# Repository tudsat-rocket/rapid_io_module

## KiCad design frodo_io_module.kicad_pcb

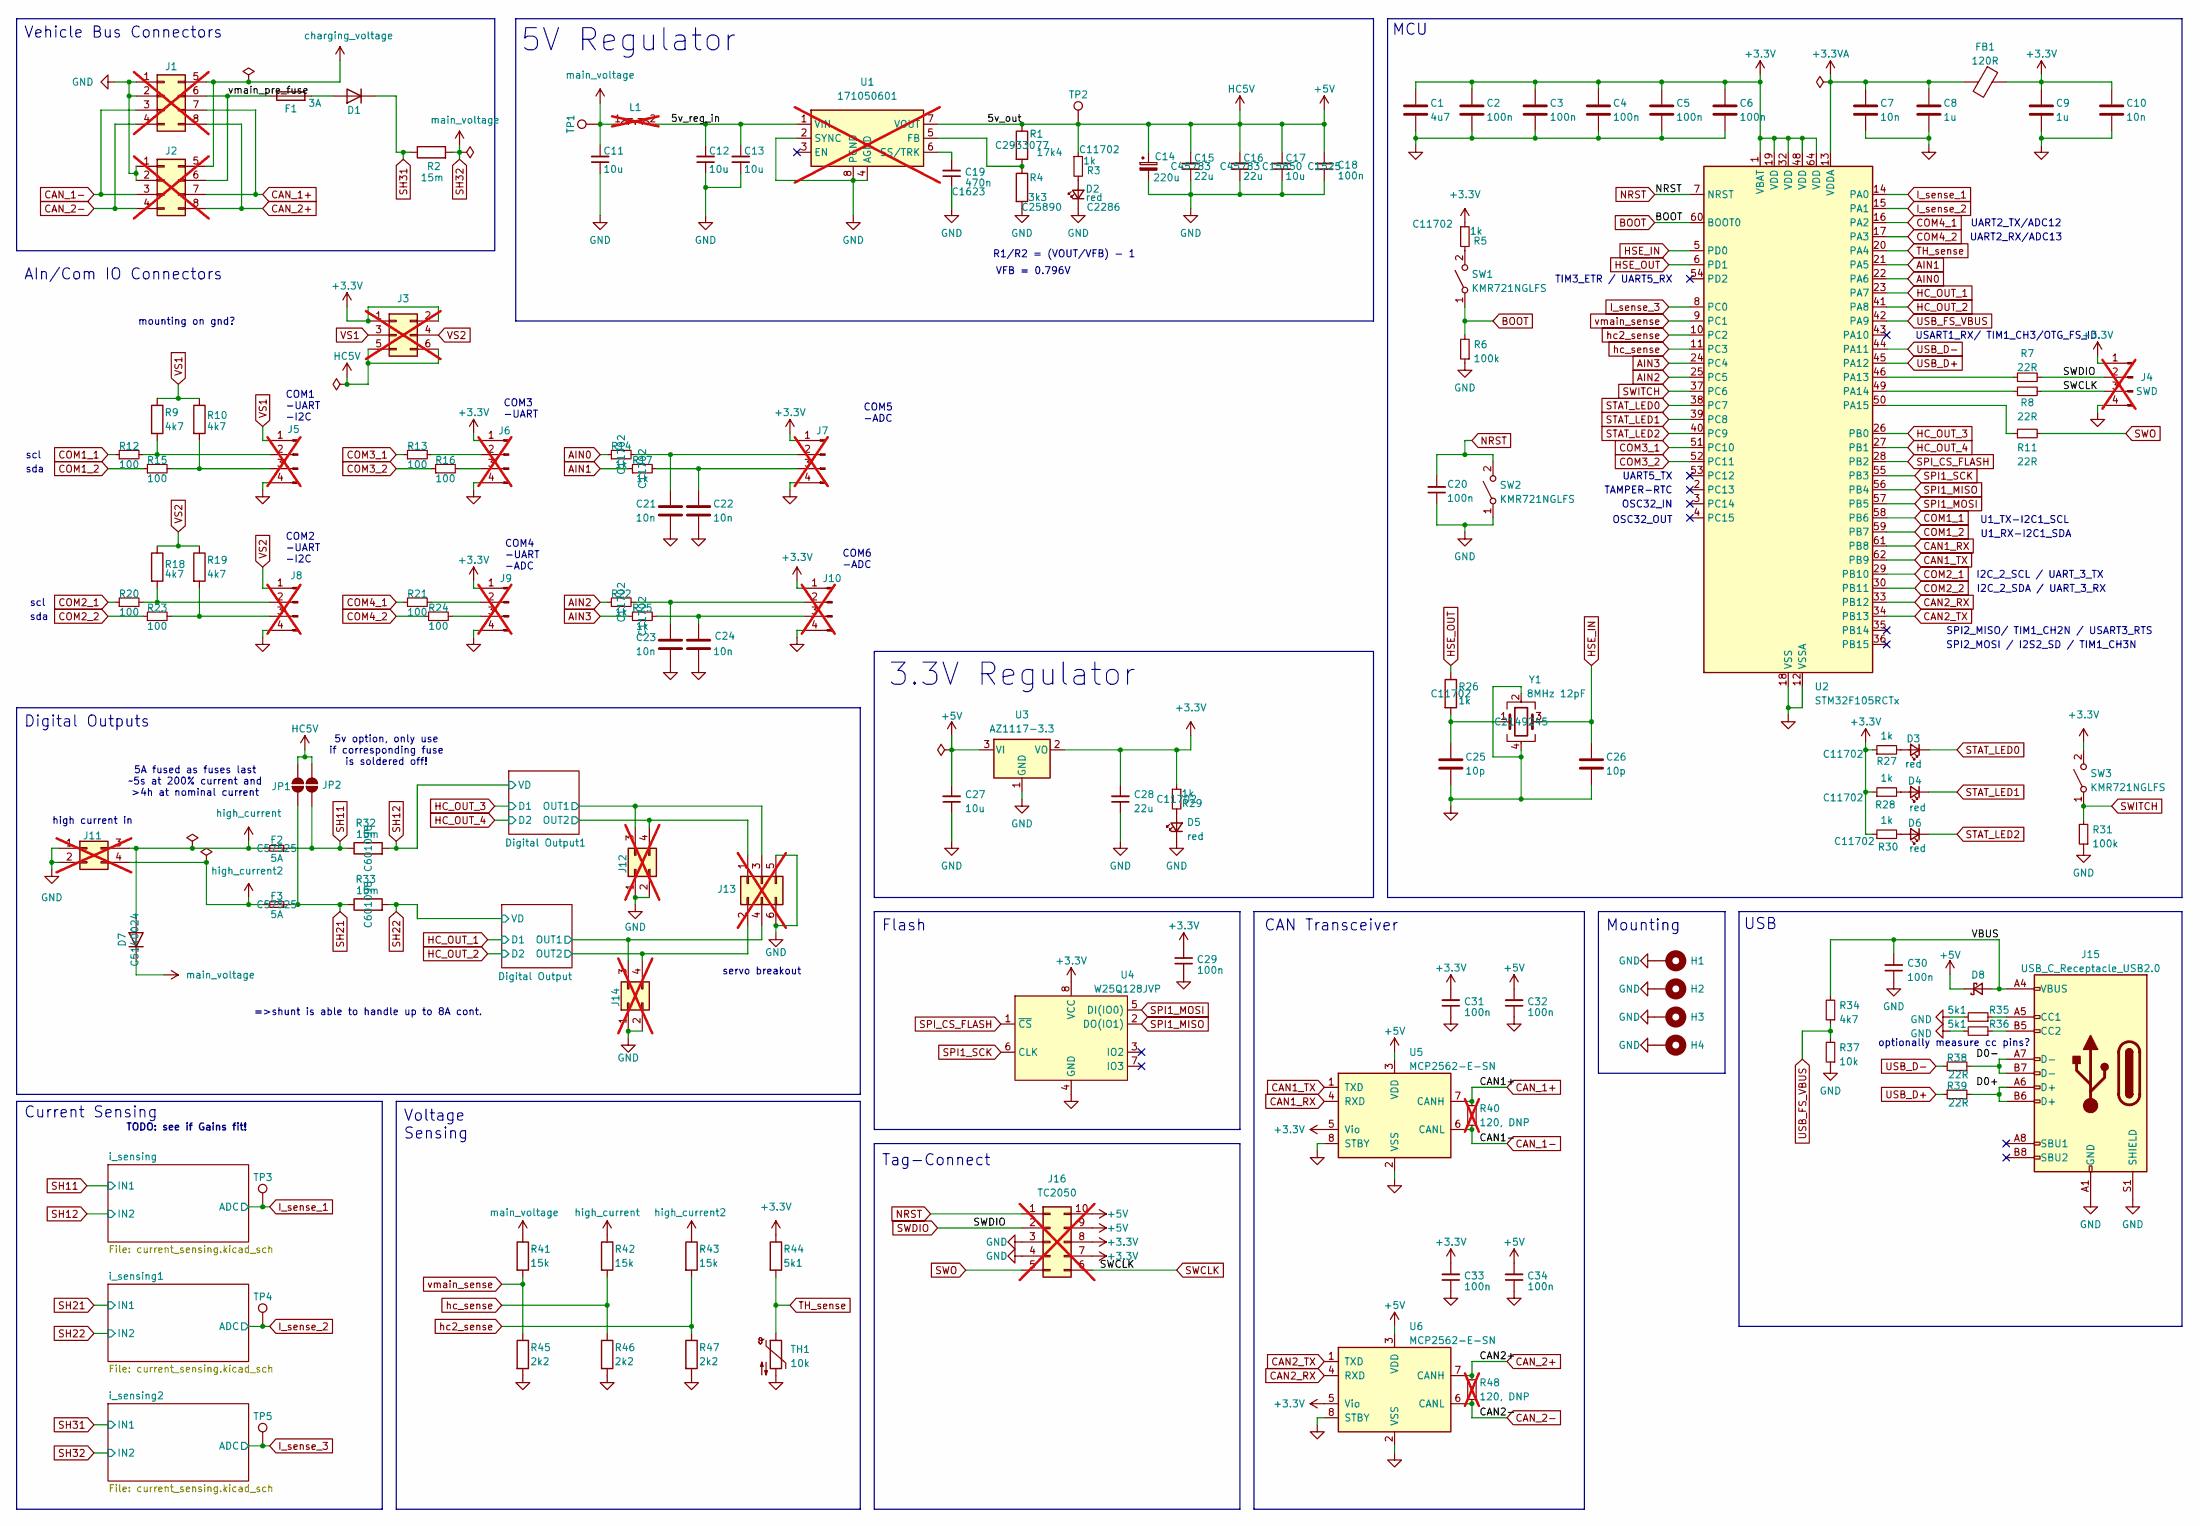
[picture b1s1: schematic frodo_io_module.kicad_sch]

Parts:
C1: 4u7; C_0402_1005Metric; LCSC# C23733
C2, C3, C4, C5, C6, C29, C31, C32, C33, C34: 100n; C_0402_1005Metric; LCSC# C1525
C7, C10: 10n; C_0402_1005Metric; LCSC# C15195
C8, C9: 1u; C_0402_1005Metric; LCSC# C52923
C11, C12, C13: 10u; C_0805_2012Metric; LCSC C440198
C14: 220u; CP_Elec_6.3x4.5; LCSC C5379968
C15, C16: 22u; C_0805_2012Metric; LCSC C45783
C17: 10u; C_0805_2012Metric; LCSC C15850
C18: 100n; C_0402_1005Metric; LCSC C1525
C19: 470n; C_0603_1608Metric; LCSC C1623
C20, C30: 100n; C_0402_1005Metric; Part# CL10B104KB8NNNC; LCSC C1525
C21, C22, C23, C24: 10n; C_0402_1005Metric; LCSC C15195
C25, C26: 10p; C_0402_1005Metric; LCSC# C32949
C27: 10u; C_0402_1005Metric; Part# CL31B106KAHNNNE; LCSC C15525
C28: 22u; C_0603_1608Metric; Part# GRM155R60J226ME11D; LCSC C59461
D1, D7: 700mV@5A; D_SMA; LCSC C5140024
D2: red; LED_0603_1608Metric; Part# XL-1608SURC-06; LCSC C2286
D3, D4, D5, D6: red; LED_0603_1608Metric; LCSC C2286
D8: D_SOD-123; Part# PMEG3020EH,115; LCSC C8598
F1: 3A; Fuse_1206_3216Metric_Pad1.42x1.75mm_HandSolder; LCSC C14165
F2, F3: 5A; Fuse_1206_3216Metric_Pad1.42x1.75mm_HandSolder; Part# 0466005.NRHF; LCSC C57525
FB1: 120R; L_0603_1608Metric; Part# BLM18PG121SN1D; LCSC# C14709
H1, H2, H3, H4: MountingHole_Pad; MountingHole_3.2mm_M3_Pad_Via; DigiKey# N/A
J1, J2: Conn_02x04_Top_Bottom; Molex_Micro-Fit_3.0_43045-0800_2x04_P3.00mm_Horizontal; LCSC x; not fitted
J3: Conn_02x03_Odd_Even; PinHeader_2x03_P1.27mm_Vertical_SMD; not fitted
J4: SWD; PinHeader_1x04_P2.54mm_Vertical; not fitted
J5, J6, J8, J9: JST-GH 4Pin; JST_GH_SM04B-GHS-TB_1x04-1MP_P1.25mm_Horizontal; not fitted
J7, J10: JST-GH 4Pin; JST_GH_BM04B-GHS-TBT_1x04-1MP_P1.25mm_Vertical; not fitted
J11: Molex_Micro-Fit_3.0_43045-0400_2x02_P3.00mm_Horizontal; LCSC# x; not fitted
J12, J14: Molex_Micro-Fit_3.0_43045-0400_2x02_P3.00mm_Horizontal; not fitted
J13: Conn_02x03_Odd_Even; PinHeader_2x03_P2.54mm_Vertical; not fitted
J15: USB_C_Receptacle_USB2.0; USB_C_Receptacle_Palconn_UTC16-G; Part# KH-TYPE-C-16P; LCSC C709357
J16: TC2050; Tag-Connect_TC2050-IDC-FP_2x05_P1.27mm_Vertical; not fitted
JP1, JP2: SolderJumper_2_Open; SolderJumper-2_P1.3mm_Open_RoundedPad1.0x1.5mm
L1: 2.2uH; L_Wurth_WE-PD2-5848; Part Number 744774022; not fitted
R1: 17k4; R_0402_1005Metric; LCSC C2933077
R2, R32, R33: 15m; R_1206_3216Metric_Pad1.30x1.75mm_HandSolder; Part# HoLR1206-1W-15mR-1%-75ppm; LCSC C601098
R3, R5, R14, R17, R22, R25, R26, R27, R28, R29, R30: 1k; R_0402_1005Metric; LCSC C11702
R4: 3k3; R_0402_1005Metric; LCSC C25890
R6, R31: 100k; R_0402_1005Metric; Part# RC0603FR-0710KL; LCSC C25741
R7, R8, R11: 22R; R_0402_1005Metric; Part# RC0603FR-0710KL; LCSC C25092
R9, R10, R18, R19: 4k7; R_0603_1608Metric_Pad0.98x0.95mm_HandSolder; LCSC C23162
R12, R13, R15, R16, R20, R21, R23, R24: 100; R_0402_1005Metric; Part# RC0402FR-07100RL; LCSC# C106232
R34: 4k7; R_0402_1005Metric; Part# RC0603FR-0710KL; LCSC C25900
R35, R36: 5k1; R_0402_1005Metric; Part# RC0603FR-075K1L; LCSC C25905
R37: 10k; R_0402_1005Metric; Part# RC0603FR-0710KL; LCSC C25744
R38, R39: 22R; R_0402_1005Metric; Part# RC0603FR-0722RL; LCSC C25092
R40, R48: 120, DNP; R_0603_1608Metric_Pad0.98x0.95mm_HandSolder; LCSC# x; not fitted
R41, R42, R43: 15k; R_0402_1005Metric; LCSC C25756
R44: 5k1; R_0402_1005Metric; LCSC C25905
R45, R46, R47: 2k2; R_0402_1005Metric; LCSC C25879
SW1, SW2, SW3: KMR721NGLFS; SW_SPST_TS-1088-xR020; Part# KMR721NGLFS; LCSC C720477
TH1: 10k; R_0603_1608Metric_Pad0.98x0.95mm_HandSolder; Part# NCP18XH103F03RB; LCSC# C13564
TP1, TP2, TP3, TP4, TP5: TestPoint; TestPoint_Pad_D1.0mm
U1: 171050601; TO-263-7_TabPin8; not fitted
U2: STM32F105RCTx; LQFP-64_10x10mm_P0.5mm; LCSC# C8345
U3: AZ1117-3.3; SOT-223-3_TabPin2; LCSC C92102
U4: W25Q128JVP; SOIC-8_5.3x5.3mm_P1.27mm; Part# W25Q128JVSIQ; LCSC# C97521
U5, U6: MCP2562-E-SN; SOIC-8_3.9x4.9mm_P1.27mm; Part# MCP2562T-E/SN; LCSC# C191417
Y1: 8MHz 12pF; Crystal_SMD_5032-4Pin_5.0x3.2mm; Part# 5TJ480000NYLBC; LCSC C2149245

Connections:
+3.3V: C1.1, C2.1, C3.1, C4.1, C5.1, C6.1, C9.1, C10.1, C28.2, C29.2, C31.2, C33.2, FB1.1, J3.1, J3.2, J4.1, J6.1, J7.1, J9.1, J10.1, J16.7, J16.8, R5.1, R27.1, R28.1, R29.1, R30.1, R44.1, SW3.2 (B), U2.1 (VBAT), U2.19 (VDD), U2.32 (VDD), U2.48 (VDD), U2.64 (VDD), U3.2 (VO), U4.8 (VCC), U5.5 (Vio), U6.5 (Vio); also elsewhere on the board
+3.3VA: C7.1, C8.1, FB1.2, U2.13 (VDDA)
+5V: C14.1, C15.2, C16.2, C17.2, C18.2, C27.2, C32.2, C34.2, D8.1 (K), J3.5, J3.6, J16.9, J16.10, JP1.2 (B), JP2.2 (B), R1.1, R3.1, TP2.1 (1_1), U1.7 (VOUT), U3.3 (VI), U5.3 (VDD), U6.3 (VDD)
/5v_reg_in: C12.2, C13.2, L1.2, U1.1 (VIN)
/D0+: J15.A6 (D+), J15.B6 (D+), R39.2
/D0-: J15.A7 (D-), J15.B7 (D-), R38.1
/Digital Output1/OUT1: J12.3, J13.3; also elsewhere on the board
/Digital Output1/OUT2: J12.4, J13.1; also elsewhere on the board
/Digital Output/OUT1: J13.4, J14.3; also elsewhere on the board
/Digital Output/OUT2: J13.2, J14.4; also elsewhere on the board
/VBUS: C30.2, D8.2 (A), J15.A4 (VBUS), J15.A9 (VBUS), J15.B4 (VBUS), J15.B9 (VBUS), R34.2
/vmain_pre_fuse: F1.1, J1.6, J2.6
AIN0: R14.1, U2.22 (PA6)
AIN1: R17.1, U2.21 (PA5)
AIN2: R22.1, U2.25 (PC5)
AIN3: R25.1, U2.24 (PC4)
BOOT: R6.2, SW1.1 (A), U2.60 (BOOT0)
CAN1_RX: U2.61 (PB8), U5.4 (RXD)
CAN1_TX: U2.62 (PB9), U5.1 (TXD)
CAN2_RX: U2.33 (PB12), U6.4 (RXD)
CAN2_TX: U2.34 (PB13), U6.1 (TXD)
CAN_1+: J1.7, J2.7, R40.1, U5.7 (CANH)
CAN_1-: J1.3, J2.3, R40.2, U5.6 (CANL)
CAN_2+: J1.8, J2.8, R48.1, U6.7 (CANH)
CAN_2-: J1.4, J2.4, R48.2, U6.6 (CANL)
COM1_1: R12.1, U2.58 (PB6)
COM1_2: R15.1, U2.59 (PB7)
COM2_1: R20.1, U2.29 (PB10)
COM2_2: R23.1, U2.30 (PB11)
COM3_1: R13.1, U2.51 (PC10)
COM3_2: R16.1, U2.52 (PC11)
COM4_1: R21.1, U2.16 (PA2)
COM4_2: R24.1, U2.17 (PA3)
GND: C1.2, C2.2, C3.2, C4.2, C5.2, C6.2, C7.2, C8.2, C9.2, C10.2, C11.1, C12.1, C13.1, C14.2, C15.1, C16.1, C17.1, C18.1, C19.1, C20.1, C21.2, C22.2, C23.2, C24.2, C25.2, C26.2, C27.1, C28.1, C29.1, C30.1, C31.1, C32.1, C33.1, C34.1, D2.1 (K), D5.1 (K), H1.1 (1_1), H2.1 (1_1), H3.1 (1_1), H4.1 (1_1), J1.1, J1.2, J2.1, J2.2, J4.4, J5.4, J6.4, J7.4, J8.4, J9.4, J10.4, J11.1, J11.2, J12.1, J12.2, J13.5, J13.6, J14.1, J14.2, J15.A1 (GND), J15.A12 (GND), J15.B1 (GND), J15.B12 (GND), J15.S1 (SHIELD), J16.3, J16.4, R4.2, R6.1, R31.1, R35.2, R36.2, R37.1, R45.2, R46.2, R47.2, SW2.1 (A), TH1.2, U1.2 (SYNC), U1.4 (AGND), U1.8 (PGND), U2.12 (VSSA), U2.18 (VSS), U2.31 (VSS), U2.47 (VSS), U2.63 (VSS), U3.1 (GND), U4.4 (GND), U5.2 (VSS), U5.8 (STBY), U6.2 (VSS), U6.8 (STBY), Y1.2, Y1.4; also elsewhere on the board
HC_OUT_1: U2.23 (PA7); also elsewhere on the board
HC_OUT_2: U2.41 (PA8); also elsewhere on the board
HC_OUT_3: U2.26 (PB0); also elsewhere on the board
HC_OUT_4: U2.27 (PB1); also elsewhere on the board
HSE_IN: C26.1, U2.5 (PD0), Y1.3
HSE_OUT: R26.1, U2.6 (PD1)
I_sense_1: TP3.1 (1_1), U2.14 (PA0); also elsewhere on the board
I_sense_2: TP4.1 (1_1), U2.15 (PA1); also elsewhere on the board
I_sense_3: TP5.1 (1_1), U2.8 (PC0); also elsewhere on the board
NRST: C20.2, J16.1, SW2.2 (B), U2.7 (NRST)
unnamed: C25.1, R26.2, Y1.1
unnamed: D1.2 (A), F1.2
unnamed: D2.2 (A), R3.2
unnamed: D3.2 (A), R27.2
unnamed: D4.2 (A), R28.2
unnamed: D5.2 (A), R29.2
unnamed: D6.2 (A), R30.2
unnamed: J5.2, R9.2, R12.2
unnamed: J5.3, R10.2, R15.2
unnamed: J6.2, R13.2
unnamed: J6.3, R16.2
unnamed: C21.1, J7.2, R14.2
unnamed: C22.1, J7.3, R17.2
unnamed: J8.2, R18.2, R20.2
unnamed: J8.3, R19.2, R23.2
unnamed: J9.2, R21.2
unnamed: J9.3, R24.2
unnamed: C23.1, J10.2, R22.2
unnamed: C24.1, J10.3, R25.2
unnamed: J15.A5 (CC1), R35.1
unnamed: J15.B5 (CC2), R36.1
unnamed: R5.2, SW1.2 (B)
unnamed: R1.2, R4.1, U1.5 (FB)
unnamed: C19.2, U1.6 (SS/TRK)
unnamed: R7.1, U2.46 (PA13)
unnamed: R8.1, U2.49 (PA14)
unnamed: R11.1, U2.50 (PA15)
SH11: F2.1, JP2.1 (A), R32.1; also elsewhere on the board
SH12: R32.2; also elsewhere on the board
SH21: F3.1, JP1.1 (A), R33.1; also elsewhere on the board
SH22: R33.2; also elsewhere on the board
SH31: D1.1 (K), R2.1; also elsewhere on the board
SH32: C11.2, D7.1 (K), L1.1, R2.2, R41.1, TP1.1 (1_1); also elsewhere on the board
SPI1_MISO: U2.56 (PB4), U4.2 (DO(IO1))
SPI1_MOSI: U2.57 (PB5), U4.5 (DI(IO0))
SPI1_SCK: U2.55 (PB3), U4.6 (CLK)
SPI_CS_FLASH: U2.28 (PB2), U4.1 (~CS)
STAT_LED0: D3.1 (K), U2.38 (PC7)
STAT_LED1: D4.1 (K), U2.39 (PC8)
STAT_LED2: D6.1 (K), U2.40 (PC9)
SWCLK: J4.3, J16.6, R8.2
SWDIO: J4.2, J16.2, R7.2
SWITCH: R31.2, SW3.1 (A), U2.37 (PC6)
SWO: J16.5, R11.2
TH_sense: R44.2, TH1.1, U2.20 (PA4)
USB_D+: R39.1, U2.45 (PA12)
USB_D-: R38.2, U2.44 (PA11)
USB_FS_VBUS: R34.1, R37.2, U2.42 (PA9)
VS1: J3.3, J5.1, R9.1, R10.1
VS2: J3.4, J8.1, R18.1, R19.1
charging_voltage: J1.5, J2.5
hc2_sense: R43.2, R47.1, U2.10 (PC2)
hc_sense: R42.2, R46.1, U2.11 (PC3)
high_current: D7.2 (A), F2.2, J11.3, R42.1
high_current2: F3.2, J11.4, R43.1
vmain_sense: R41.2, R45.1, U2.9 (PC1)

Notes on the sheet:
scl
Vehicle Bus Connectors
servo breakout
3.3V Regulator
TIM3_ETR / UART5_RX
U1_RX-I2C1_SDA
SPI2_MISO/ TIM1_CH2N / USART3_RTS
OSC32_IN
I2C_2_SCL / UART_3_TX
VFB = 0.796V
USART1_RX/ TIM1_CH3/OTG_FS_ID
COM4 -UART -ADC
Mounting
OSC32_OUT
COM2 -UART -I2C
COM6 -ADC
5v option, only use if corresponding fuse is soldered off!
USB
5A fused as fuses last ~5s at 200% current and >4h at nominal current
Voltage Sensing
CAN Transceiver
TODO: see if Gains fit!
=>shunt is able to handle up to 8A cont.
U1_TX-I2C1_SCL
optionally measure cc pins?
COM3 -UART
AIn/Com IO Connectors
UART2_RX/ADC13
SPI2_MOSI / I2S2_SD / TIM1_CH3N
sda
5V Regulator
UART5_TX
Digital Outputs
R1/R2 = (VOUT/VFB) - 1
MCU
TAMPER-RTC
UART2_TX/ADC12
Current Sensing
high current in
mounting on gnd?

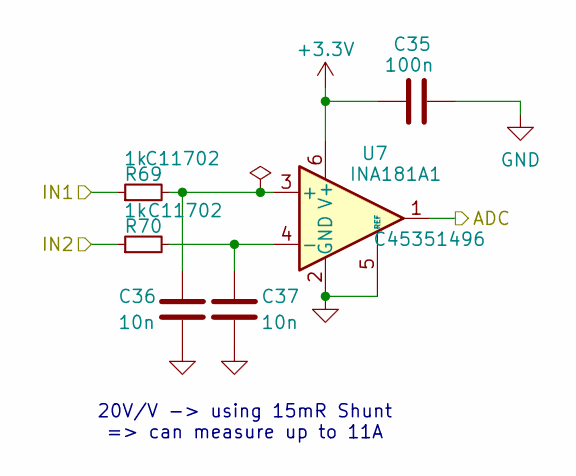
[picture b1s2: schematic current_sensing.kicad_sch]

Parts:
C35: 100n; C_0402_1005Metric; LCSC# C1525
C36, C37: 10n; C_0402_1005Metric; LCSC C15195
R69, R70: 1k; R_0402_1005Metric; LCSC C11702
U7: INA181A1; SOT-23-6; LCSC C45351496

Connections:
+3.3V: C35.1, U7.6 (V+); also elsewhere on the board
GND: C35.2, C36.2, C37.2, U7.2 (GND), U7.5 (REF); also elsewhere on the board
I_sense_1: U7.1; also elsewhere on the board
unnamed: C36.1, R69.2, U7.3 (+)
unnamed: C37.1, R70.2, U7.4 (-)
SH11: R69.1; also elsewhere on the board
SH12: R70.1; also elsewhere on the board

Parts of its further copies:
C38, C41: 100n; C_0402_1005Metric; LCSC# C1525
C39, C40, C42, C43: 10n; C_0402_1005Metric; LCSC C15195
R71, R72, R73, R74: 1k; R_0402_1005Metric; LCSC C11702
U8, U9: INA181A1; SOT-23-6; LCSC C45351496

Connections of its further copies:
+3.3V: C38.1, C41.1, U8.6 (V+), U9.6 (V+); also elsewhere on the board
GND: C38.2, C39.2, C40.2, C41.2, C42.2, C43.2, U8.2 (GND), U8.5 (REF), U9.2 (GND), U9.5 (REF); also elsewhere on the board
I_sense_2: U8.1; also elsewhere on the board
I_sense_3: U9.1; also elsewhere on the board
unnamed: C39.1, R71.2, U8.3 (+)
unnamed: C40.1, R72.2, U8.4 (-)
unnamed: C42.1, R73.2, U9.3 (+)
unnamed: C43.1, R74.2, U9.4 (-)
SH21: R71.1; also elsewhere on the board
SH22: R72.1; also elsewhere on the board
SH31: R73.1; also elsewhere on the board
SH32: R74.1; also elsewhere on the board

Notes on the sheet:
20V/V -> using 15mR Shunt => can measure up to 11A

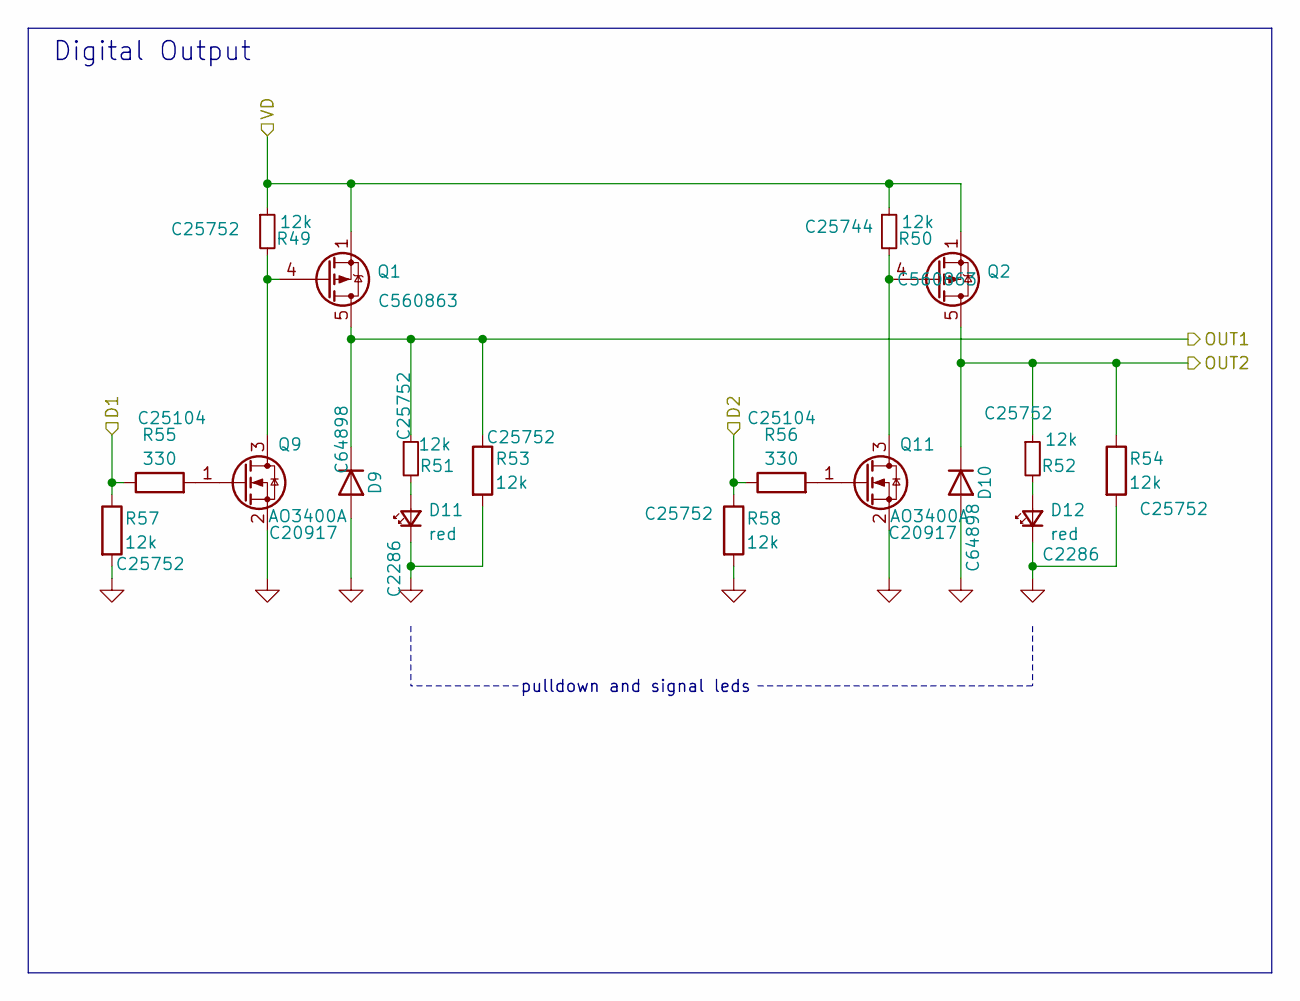
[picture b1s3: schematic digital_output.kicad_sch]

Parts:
D9, D10: D; D_SOD-123FL; LCSC C64898
D11, D12: red; LED_0603_1608Metric; LCSC C2286
Q1, Q2: AOSP21321; SOIC-8_3.9x4.9mm_P1.27mm; Part# AOSP21321; LCSC C560863
Q9, Q11: AO3400A; SOT-23; LCSC C20917
R49, R51, R52, R53, R54, R57, R58: 12k; R_0402_1005Metric; LCSC C25752
R50: 12k; R_0402_1005Metric; LCSC C25744
R55, R56: 330; R_0402_1005Metric; LCSC C25104

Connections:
/Digital Output/OUT1: D9.1 (K), Q1.5 (D), Q1.6 (D), Q1.7 (D), Q1.8 (D), R51.1, R53.1; also elsewhere on the board
/Digital Output/OUT2: D10.1 (K), Q2.5 (D), Q2.6 (D), Q2.7 (D), Q2.8 (D), R52.1, R54.1; also elsewhere on the board
GND: D9.2 (A), D10.2 (A), D11.1 (K), D12.1 (K), Q9.2 (S), Q11.2 (S), R53.2, R54.2, R57.2, R58.2; also elsewhere on the board
HC_OUT_1: R55.1, R57.1; also elsewhere on the board
HC_OUT_2: R56.1, R58.1; also elsewhere on the board
unnamed: D11.2 (A), R51.2
unnamed: D12.2 (A), R52.2
unnamed: Q1.4 (G), Q9.3 (D), R49.2
unnamed: Q9.1 (G), R55.2
unnamed: Q2.4 (G), Q11.3 (D), R50.2
unnamed: Q11.1 (G), R56.2
SH22: Q1.1 (S), Q1.2 (S), Q1.3 (S), Q2.1 (S), Q2.2 (S), Q2.3 (S), R49.1, R50.1; also elsewhere on the board

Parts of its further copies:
D13, D14: D; D_SOD-123FL; LCSC C64898
D15, D16: red; LED_0603_1608Metric; LCSC C2286
Q5, Q6: AOSP21321; SOIC-8_3.9x4.9mm_P1.27mm; Part# AOSP21321; LCSC C560863
Q10, Q12: AO3400A; SOT-23; LCSC C20917
R59, R61, R62, R63, R64, R67, R68: 12k; R_0402_1005Metric; LCSC C25752
R60: 12k; R_0402_1005Metric; LCSC C25744
R65, R66: 330; R_0402_1005Metric; LCSC C25104

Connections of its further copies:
/Digital Output1/OUT1: D13.1 (K), Q5.5 (D), Q5.6 (D), Q5.7 (D), Q5.8 (D), R61.1, R63.1; also elsewhere on the board
/Digital Output1/OUT2: D14.1 (K), Q6.5 (D), Q6.6 (D), Q6.7 (D), Q6.8 (D), R62.1, R64.1; also elsewhere on the board
GND: D13.2 (A), D14.2 (A), D15.1 (K), D16.1 (K), Q10.2 (S), Q12.2 (S), R63.2, R64.2, R67.2, R68.2; also elsewhere on the board
HC_OUT_3: R65.1, R67.1; also elsewhere on the board
HC_OUT_4: R66.1, R68.1; also elsewhere on the board
unnamed: D15.2 (A), R61.2
unnamed: D16.2 (A), R62.2
unnamed: Q5.4 (G), Q10.3 (D), R59.2
unnamed: Q10.1 (G), R65.2
unnamed: Q6.4 (G), Q12.3 (D), R60.2
unnamed: Q12.1 (G), R66.2
SH12: Q5.1 (S), Q5.2 (S), Q5.3 (S), Q6.1 (S), Q6.2 (S), Q6.3 (S), R59.1, R60.1; also elsewhere on the board

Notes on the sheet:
pulldown and signal leds
Digital Output

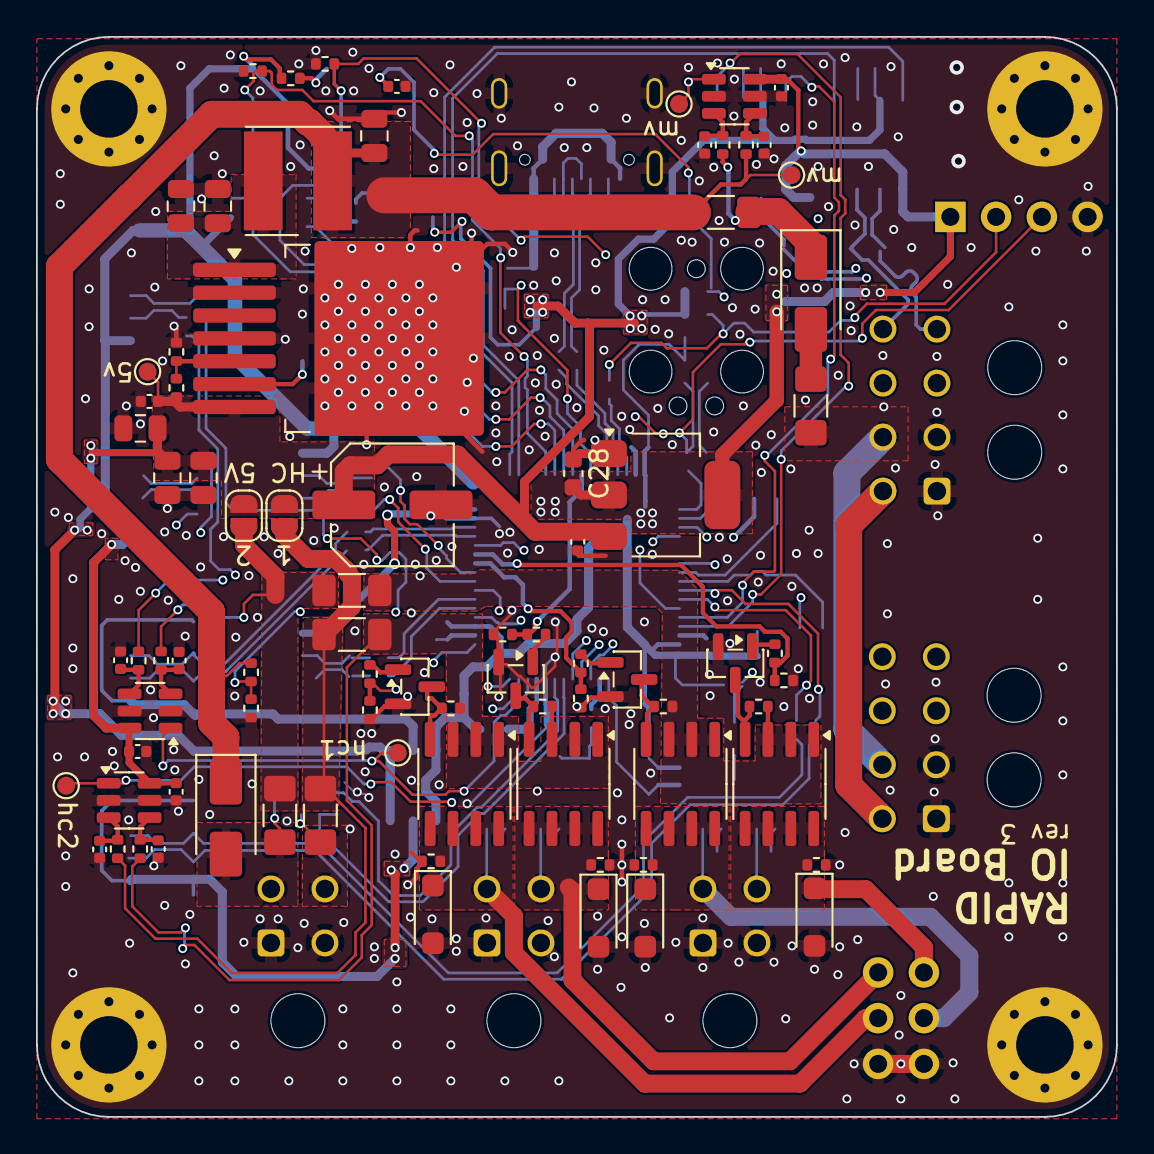
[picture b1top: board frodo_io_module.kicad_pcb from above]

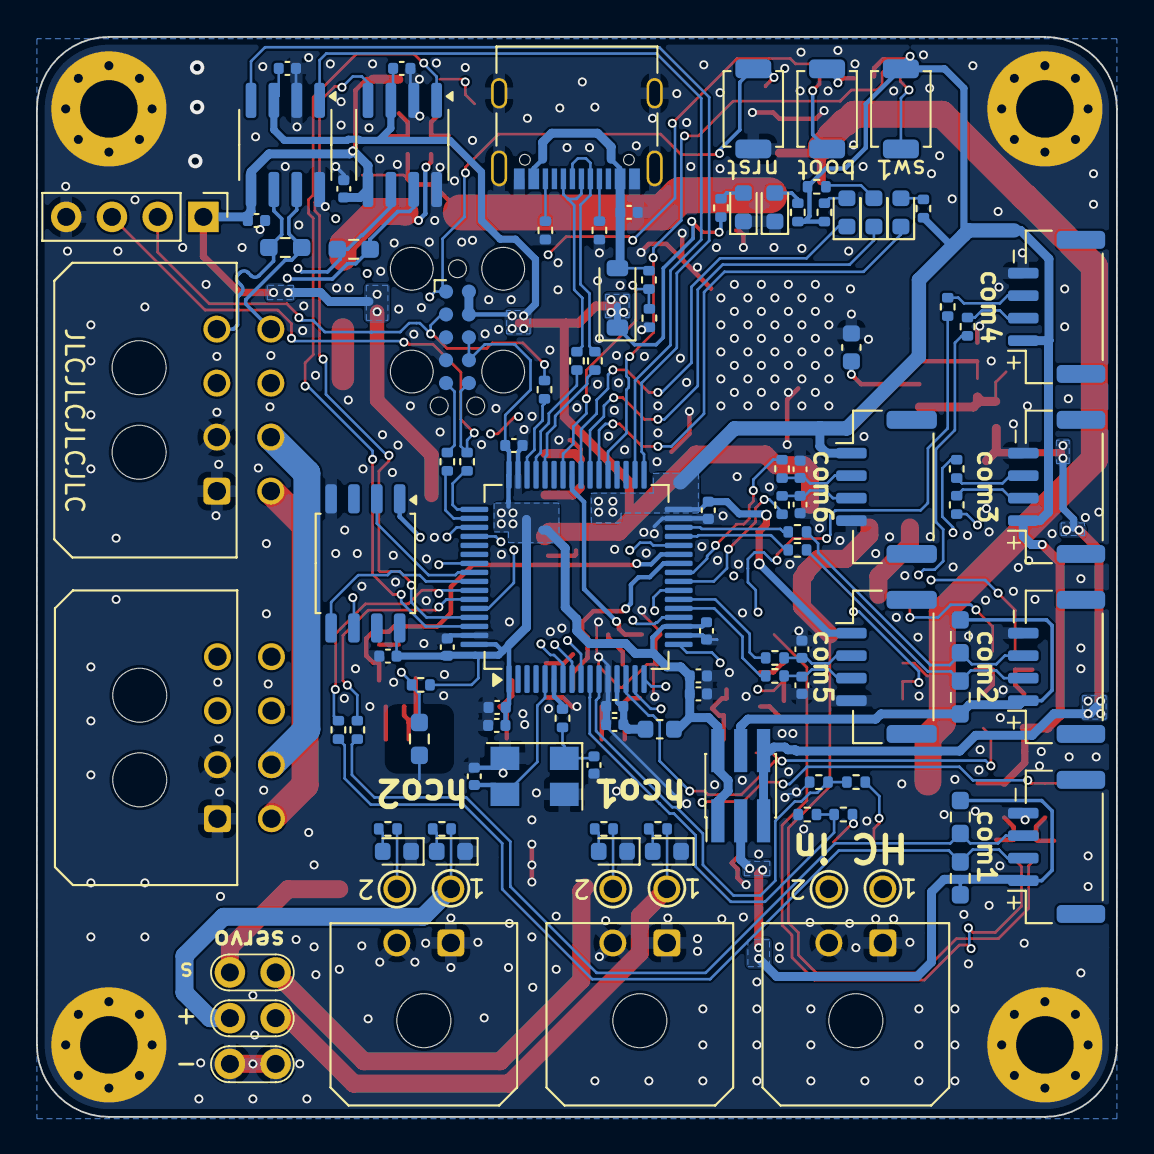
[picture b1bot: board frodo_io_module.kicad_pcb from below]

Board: 4 copper layers, 60.0 x 60.0 mm, 187 parts (101 on the bottom side), 118 nets.

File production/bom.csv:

Designator,Footprint,Quantity,Value,LCSC Part #
C1,0402,1,4u7,
"C10, C7",0402,2,10n,
"C11, C12, C13",0805,3,10u,C440198
C14,CP_Elec_6.3x4.5,1,220u,C5379968
"C15, C16",0805,2,22u,C45783
C17,0805,1,10u,C15850 
"C18, C20, C30",0402,3,100n,C1525
C19,0603,1,470n,C1623
"C2, C29, C3, C31, C32, C33, C34, C35, C38, C4, C41, C5, C6",0402,13,100n,
"C21, C22, C23, C24, C36, C37, C39, C40, C42, C43",0402,10,10n,C15195
"C25, C26",0402,2,10p,
C27,0402,1,10u,C15525
C28,0603,1,22u,C59461
"C8, C9",0402,2,1u,
"D1, D7",D_SMA,2,700mV@5A,C5140024
"D10, D13, D14, D9",D_SOD-123FL,4,D, C64898
"D11, D12, D15, D16, D2, D3, D4, D5, D6",0603,9,red,C2286
D8,D_SOD-123,1,~,C8598
F1,1206,1,3A,C14165
"F2, F3",1206,2,5A,C57525
FB1,0603,1,120R,
J15,USB_C_Receptacle_Palconn_UTC16-G,1,USB_C_Receptacle_USB2.0,C709357
"Q1, Q2, Q5, Q6",SOIC-8_3.9x4.9mm_P1.27mm,4,AOSP21321,C560863
"Q10, Q11, Q12, Q9",SOT-23,4,AO3400A,C20917
R1,0402,1,17k4,C2933077
"R10, R18, R19, R9",0603,4,4k7,C23162
"R11, R7, R8",0402,3,22R,C25092
"R12, R13, R15, R16, R20, R21, R23, R24",0402,8,100,
"R14, R17, R22, R25, R26, R27, R28, R29, R3, R30, R5, R69, R70, R71, R72, R73, R74",0402,17,1k,C11702
"R2, R32, R33",1206,3,15m,C601098
"R31, R6",0402,2,100k,C25741
R34,0402,1,4k7,C25900
"R35, R36, R44",0402,3,5k1,C25905
R37,0402,1,10k,C25744
"R38, R39",0402,2,22,C25092
R4,0402,1,3k3,C25890
"R41, R42, R43",0402,3,15k,C25756
"R45, R46, R47",0402,3,2k2,C25879
"R49, R51, R52, R53, R54, R57, R58, R59, R61, R62, R63, R64, R67, R68",0402,14,12k,C25752
"R50, R60",0402,2,12k,C25744
"R55, R56, R65, R66",0402,4,330,C25104
"SW1, SW2, SW3",SW_SPST_TS-1088-xR020,3,KMR721NGLFS,C720477
TH1,0603,1,10k,
"TP1, TP2, TP3, TP4, TP5",TestPoint_Pad_D1.0mm,5,TestPoint,
U2,LQFP-64_10x10mm_P0.5mm,1,STM32F105RCTx,
U3,SOT-223-3_TabPin2,1,AZ1117-3.3,C92102
U4,SOIC-8_5.3x5.3mm_P1.27mm,1,W25Q128JVP,
"U5, U6",SOIC-8_3.9x4.9mm_P1.27mm,2,MCP2562-E-SN,
"U7, U8, U9",SOT-23-6,3,INA181A1,C45351496
Y1,Crystal_SMD_5032-4Pin_5.0x3.2mm,1,8MHz 12pF,C2149245

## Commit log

2023-12-28 basic microcontroller peripherals
2024-01-06 USART Pin Configuration
2024-01-09 voltage regulator addition
2024-01-29 dip switch addition
2024-01-29 mosfet addition
2024-02-27 label addition and switch changes
2024-03-07 mosfet
2024-03-07 dip s
2024-03-08 cleanup/commenting for better readability, minor corrections
2024-03-16 Add flash, CAN transceiver, 5V regulators, power filtering; minor corrections
2024-03-17 Add boost converter schematics
2024-03-17 Add test points
2024-03-17 Add I2C pull-up resistors and digital output flyback diodes
2024-03-17 Add voltage sensing, Correct resistor value
2024-03-29 footprints assigned
2024-03-29 more footprints assigned
2024-03-30 Finish footprint assignment
2024-06-03 updates to the schematics, rough component placement in the PCB layout
2024-06-03 trace routing of boost converter section
2024-06-08 Resolved conflicts
2024-06-19 routing traces
2024-06-21 recovery of schematics while keeping routed traces
2024-06-24 trace routing in component subgroups
2024-06-24 add 3d models for Molex connectors and power inductor
2024-07-01 routing of power levels
2024-07-01 add logos, name and revision text
2024-07-01 route traces to JST-GH connectors and ICs, fix problem with swapped CAN Bus lines
2024-07-02 finish trace routing
2024-07-04 placement of default silkscreen symbols
2024-07-04 add descriptors on silkscreen, add part numbers
2024-07-08 Firmware initial commit
2024-07-15 Implement first draft of firmware
2024-07-20 Add LEDs to ACS role
2024-07-27 Implement most of the ACS & recovery behaviour
2024-08-04 Reenable boost converter on ACS boards
    Inputs temporarily disabled until we're sharing the I2C bus.
2024-08-04 Add boost module
2024-09-02 Adjust ACS values
2024-09-22 Reuse single vref sample, invert current calculation
2024-09-22 Remove auto-toggling of outputs based on flight mode
2024-09-22 Include COM3 GPIO inputs in recovery sensor messages
2024-09-25 Reconfigure ACS IO board for charge bus drive voltage
2024-11-18 add readme
2024-12-02 add install instructions
2024-12-02 fix md
2024-12-02 fix typo
2024-12-02 replace outdated instructions
2024-12-04 fix instructions
2025-02-25 removed boost converter
2025-02-25 added vehicle bus
2025-04-08 minor changes
2025-04-16 updated scematic to new requirements
2025-04-18 some more changes to the io board
2025-04-19 pin assignments
2025-04-27 Organize Components into groups.
2025-04-28 some more pin assignments
2025-04-29 finished pin assignment, some changes to scematic
2025-05-06 work on usb connector routing
2025-05-07 fixed usb and some other issues
2025-05-07 fixed usb, added footprints
2025-05-07 some more changes
2025-05-21 rough placement of the components
2025-05-26 basic routing
2025-06-02 more routing
2025-06-02 remove second 3.3V reg and i2c pull up jumpers
2025-06-10 power routing
2025-06-15 finish routing
2025-06-23 small routing improvements
2025-07-03 added part numbers for all parts
2025-07-07 improve silkscreen
2025-07-07 Fix ouput silkscreen number, clearance violation, start skew tuning (CAN)
2025-07-10 Revisit can trace tuning
2026-02-16 started new design iteration, some scematic fixes (servo pwm&5v option, tsv issue)
2026-02-16 added comment for mosfet todo
2026-02-23 fixed transistor rotation issue, filter vs farrite bead, 5V supply for servos, and others in scematic
2026-05-20 started routing
2026-05-20 added sub scematics
2026-06-11 finished routing
2026-06-11 started silkscrean
2026-06-12 some silcscreen
2026-06-17 most current state, adapt thermal cutouts in layers
2026-06-23 high current inputs: change pmos pullup and led resistors
    Apparently Kicad also saved files in a new format.
    I was using Kicad version 10.0
2026-06-26 silkscreen improvements, change mosfets, fix diode footprint
2026-06-26 some cosmetic changes
2026-06-27 some last adaptaions while ordering
2026-06-29 order version
